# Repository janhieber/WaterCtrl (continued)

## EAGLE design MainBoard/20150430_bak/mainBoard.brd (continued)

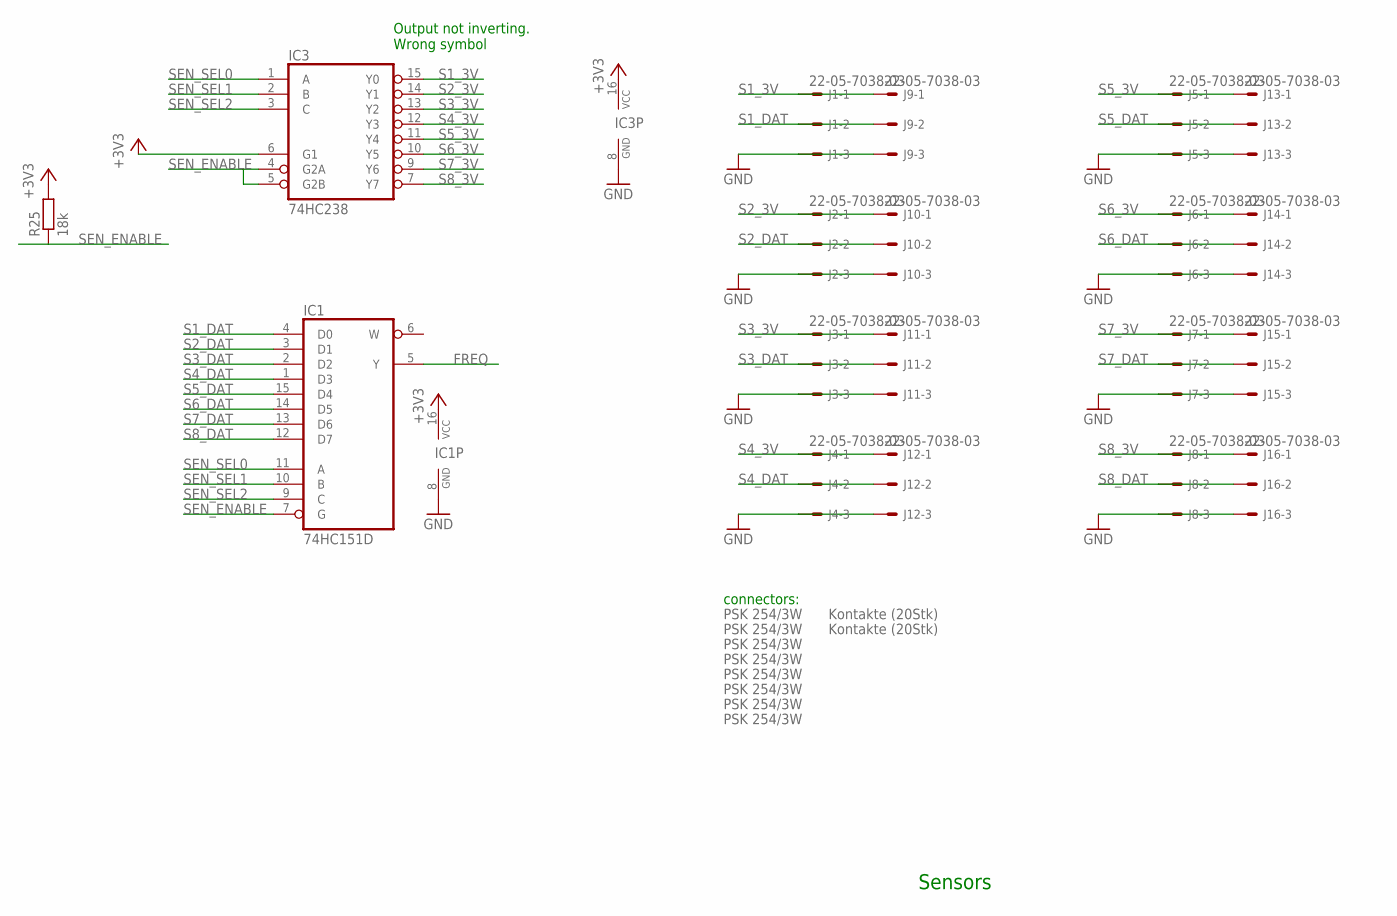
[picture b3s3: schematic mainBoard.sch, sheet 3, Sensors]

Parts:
IC1: 74HC151D; SO16
IC3: 74HC238; SO16
J1, J2, J3, J4, J5, J6, J7, J8, J9, J10, J11, J12, J13, J14, J15, J16: 22-05-7038-03; 7395-03
R25: 18k; R0805
U$3, U$4, U$5, U$6, U$7, U$8, U$9, U$10: PSK 254/3W; DUMMY_BOM
U$18, U$19: Kontakte (20Stk); DUMMY_BOM

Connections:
+3V3: IC1.16 (VCC), IC3.6 (G1), IC3.16 (VCC), R25.2; also elsewhere on the board
FREQ: IC1.5 (Y); also elsewhere on the board
GND: IC1.8 (GND), IC3.8 (GND), J1.3, J2.3, J3.3, J4.3, J5.3, J6.3, J7.3, J8.3, J9.3, J10.3, J11.3, J12.3, J13.3, J14.3, J15.3, J16.3; also elsewhere on the board
S1_3V: IC3.15 (Y0), J1.1, J9.1
S1_DAT: IC1.4 (D0), J1.2, J9.2
S2_3V: IC3.14 (Y1), J2.1, J10.1
S2_DAT: IC1.3 (D1), J2.2, J10.2
S3_3V: IC3.13 (Y2), J3.1, J11.1
S3_DAT: IC1.2 (D2), J3.2, J11.2
S4_3V: IC3.12 (Y3), J4.1, J12.1
S4_DAT: IC1.1 (D3), J4.2, J12.2
S5_3V: IC3.11 (Y4), J5.1, J13.1
S5_DAT: IC1.15 (D4), J5.2, J13.2
S6_3V: IC3.10 (Y5), J6.1, J14.1
S6_DAT: IC1.14 (D5), J6.2, J14.2
S7_3V: IC3.9 (Y6), J7.1, J15.1
S7_DAT: IC1.13 (D6), J7.2, J15.2
S8_3V: IC3.7 (Y7), J8.1, J16.1
S8_DAT: IC1.12 (D7), J8.2, J16.2
SEN_ENABLE: IC1.7 (G), IC3.4 (G2A), IC3.5 (G2B), R25.1; also elsewhere on the board
SEN_SEL0: IC1.11 (A), IC3.1 (A); also elsewhere on the board
SEN_SEL1: IC1.10 (B), IC3.2 (B); also elsewhere on the board
SEN_SEL2: IC1.9 (C), IC3.3 (C); also elsewhere on the board

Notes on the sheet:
Output not inverting. Wrong symbol
connectors:
Sensors

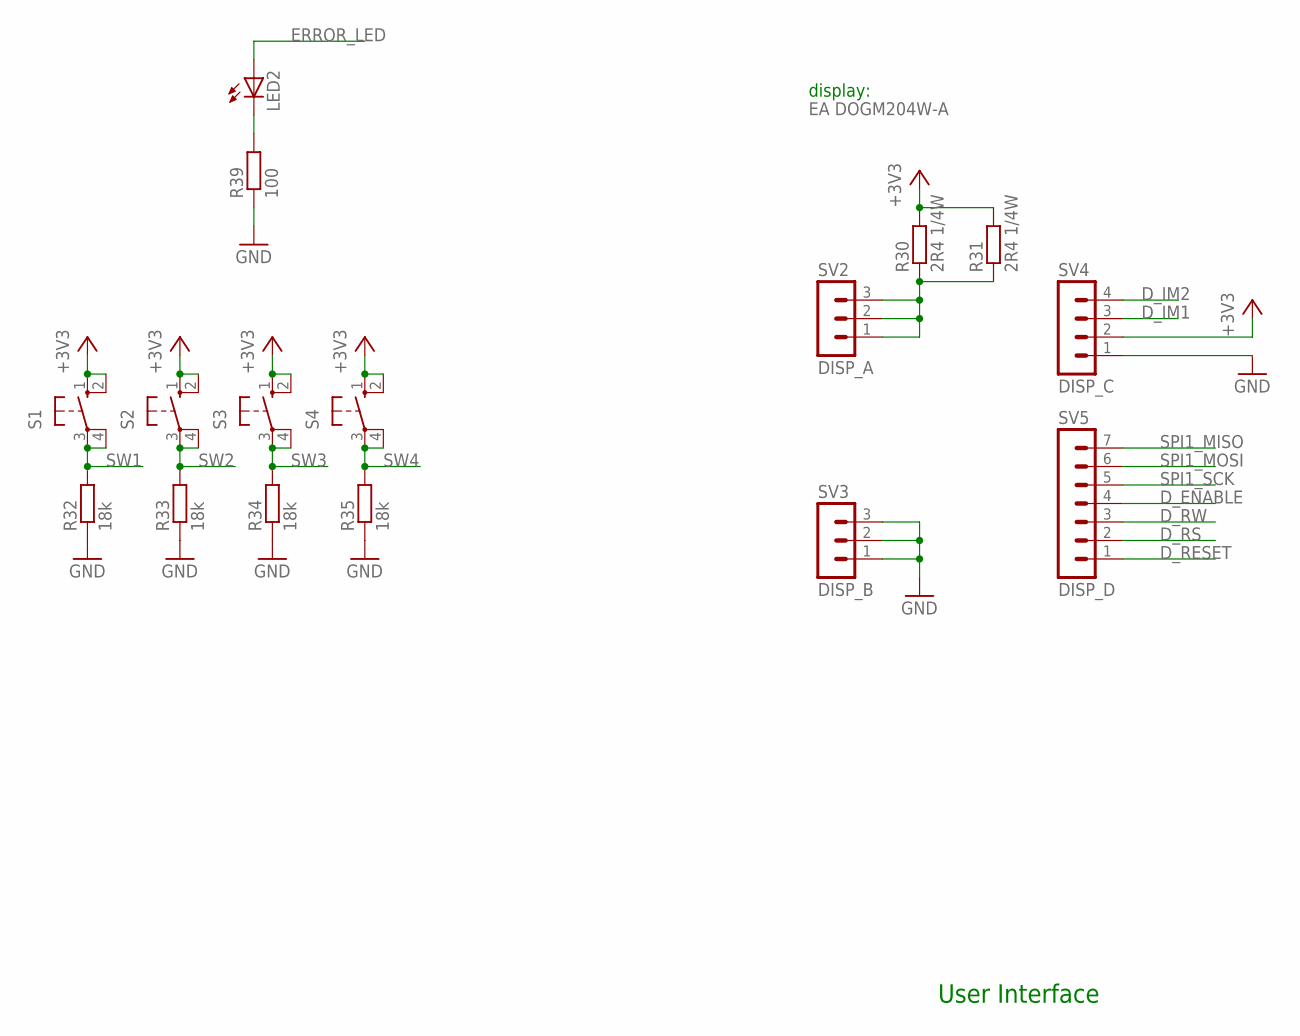
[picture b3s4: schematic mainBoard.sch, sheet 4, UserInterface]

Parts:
LED2: LED3MM
R30, R31: 2R4 1/4W; R1206
R32, R33, R34, R35: 18k; R0805
R39: 100; R0805
S1, S2, S3, S4: 10-XX; B3F-10XX
SV2: DISP_A; MA03-1
SV3: DISP_B; MA03-1
SV4: DISP_C; MA04-1
SV5: DISP_D; MA07-1
U$11: EA DOGM204W-A; DUMMY_BOM

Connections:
+3V3: R30.2, R31.2, S1.1 (S), S1.2 (S1), S2.1 (S), S2.2 (S1), S3.1 (S), S3.2 (S1), S4.1 (S), S4.2 (S1), SV4.2; also elsewhere on the board
D_ENABLE: SV5.4; also elsewhere on the board
D_IM1: SV4.3; also elsewhere on the board
D_IM2: SV4.4; also elsewhere on the board
D_RESET: SV5.1; also elsewhere on the board
D_RS: SV5.2; also elsewhere on the board
D_RW: SV5.3; also elsewhere on the board
ERROR_LED: LED2.A; also elsewhere on the board
GND: R32.1, R33.1, R34.1, R35.1, R39.1, SV3.1, SV3.2, SV3.3, SV4.1; also elsewhere on the board
unnamed: R30.1, R31.1, SV2.1, SV2.2, SV2.3
unnamed: LED2.K (C), R39.2
SPI1_MISO: SV5.7; also elsewhere on the board
SPI1_MOSI: SV5.6; also elsewhere on the board
SPI1_SCK: SV5.5; also elsewhere on the board
SW1: R32.2, S1.3, S1.4 (P1)
SW2: R33.2, S2.3, S2.4 (P1)
SW3: R34.2, S3.3, S3.4 (P1)
SW4: R35.2, S4.3, S4.4 (P1)

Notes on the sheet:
User Interface
display:

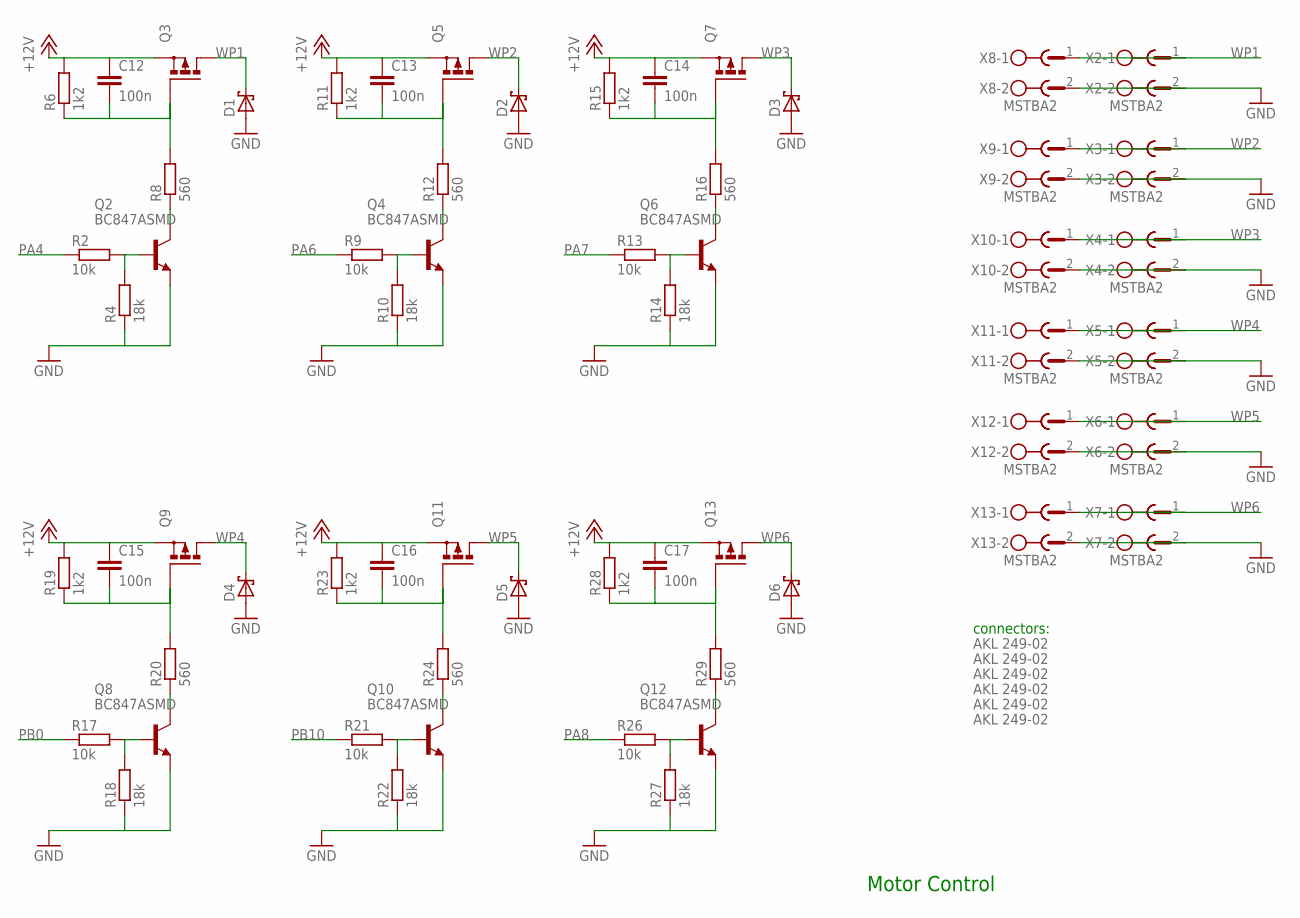
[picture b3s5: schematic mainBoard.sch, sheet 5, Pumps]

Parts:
C12, C13, C14, C15, C16, C17: 100n; C0805
D1, D2, D3, D4, D5, D6: SCHOTTKY-DIODESMC; SMC
Q2, Q4, Q6, Q8, Q10, Q12: BC847ASMD; SOT23
Q3, Q5, Q7, Q9, Q11, Q13: P-MOSFET-SO8; SO-08
R2, R9, R13, R17, R21, R26: 10k; R0805
R4, R10, R14, R18, R22, R27: 18k; R0805
R6, R11, R15, R19, R23, R28: 1k2; R0805
R8, R12, R16, R20, R24, R29: 560; R0805
U$12, U$13, U$14, U$15, U$16, U$17: AKL 249-02; DUMMY_BOM
X2, X3, X4, X5, X6, X7, X8, X9, X10, X11, X12, X13: MSTBA2

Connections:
+12V: C12.1, C13.1, C14.1, C15.1, C16.1, C17.1, Q3.1 (S), Q3.2 (S), Q3.3 (S), Q5.1 (S), Q5.2 (S), Q5.3 (S), Q7.1 (S), Q7.2 (S), Q7.3 (S), Q9.1 (S), Q9.2 (S), Q9.3 (S), Q11.1 (S), Q11.2 (S), Q11.3 (S), Q13.1 (S), Q13.2 (S), Q13.3 (S), R6.2, R11.2, R15.2, R19.2, R23.2, R28.2; also elsewhere on the board
GND: D1.A, D2.A, D3.A, D4.A, D5.A, D6.A, Q2.2 (E), Q4.2 (E), Q6.2 (E), Q8.2 (E), Q10.2 (E), Q12.2 (E), R4.1, R10.1, R14.1, R18.1, R22.1, R27.1, X2.2, X3.2, X4.2, X5.2, X6.2, X7.2, X8.2, X9.2, X10.2, X11.2, X12.2, X13.2; also elsewhere on the board
unnamed: C13.2, Q5.4 (G), R11.1, R12.2
unnamed: C12.2, Q3.4 (G), R6.1, R8.2
unnamed: Q2.3 (C), R8.1
unnamed: Q2.1 (B), R2.2, R4.2
unnamed: Q4.3 (C), R12.1
unnamed: Q4.1 (B), R9.2, R10.2
unnamed: C14.2, Q7.4 (G), R15.1, R16.2
unnamed: Q6.3 (C), R16.1
unnamed: Q6.1 (B), R13.2, R14.2
unnamed: C15.2, Q9.4 (G), R19.1, R20.2
unnamed: Q8.3 (C), R20.1
unnamed: Q8.1 (B), R17.2, R18.2
unnamed: C16.2, Q11.4 (G), R23.1, R24.2
unnamed: Q10.3 (C), R24.1
unnamed: Q10.1 (B), R21.2, R22.2
unnamed: C17.2, Q13.4 (G), R28.1, R29.2
unnamed: Q12.3 (C), R29.1
unnamed: Q12.1 (B), R26.2, R27.2
PA4: R2.1; also elsewhere on the board
PA6: R9.1; also elsewhere on the board
PA7: R13.1; also elsewhere on the board
PA8: R26.1; also elsewhere on the board
PB0: R17.1; also elsewhere on the board
PB10: R21.1; also elsewhere on the board
WP1: D1.C, Q3.5 (D), Q3.6 (D), Q3.7 (D), Q3.8 (D), X2.1, X8.1
WP2: D2.C, Q5.5 (D), Q5.6 (D), Q5.7 (D), Q5.8 (D), X3.1, X9.1
WP3: D3.C, Q7.5 (D), Q7.6 (D), Q7.7 (D), Q7.8 (D), X4.1, X10.1
WP4: D4.C, Q9.5 (D), Q9.6 (D), Q9.7 (D), Q9.8 (D), X5.1, X11.1
WP5: D5.C, Q11.5 (D), Q11.6 (D), Q11.7 (D), Q11.8 (D), X6.1, X12.1
WP6: D6.C, Q13.5 (D), Q13.6 (D), Q13.7 (D), Q13.8 (D), X7.1, X13.1

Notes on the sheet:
Motor Control
connectors:

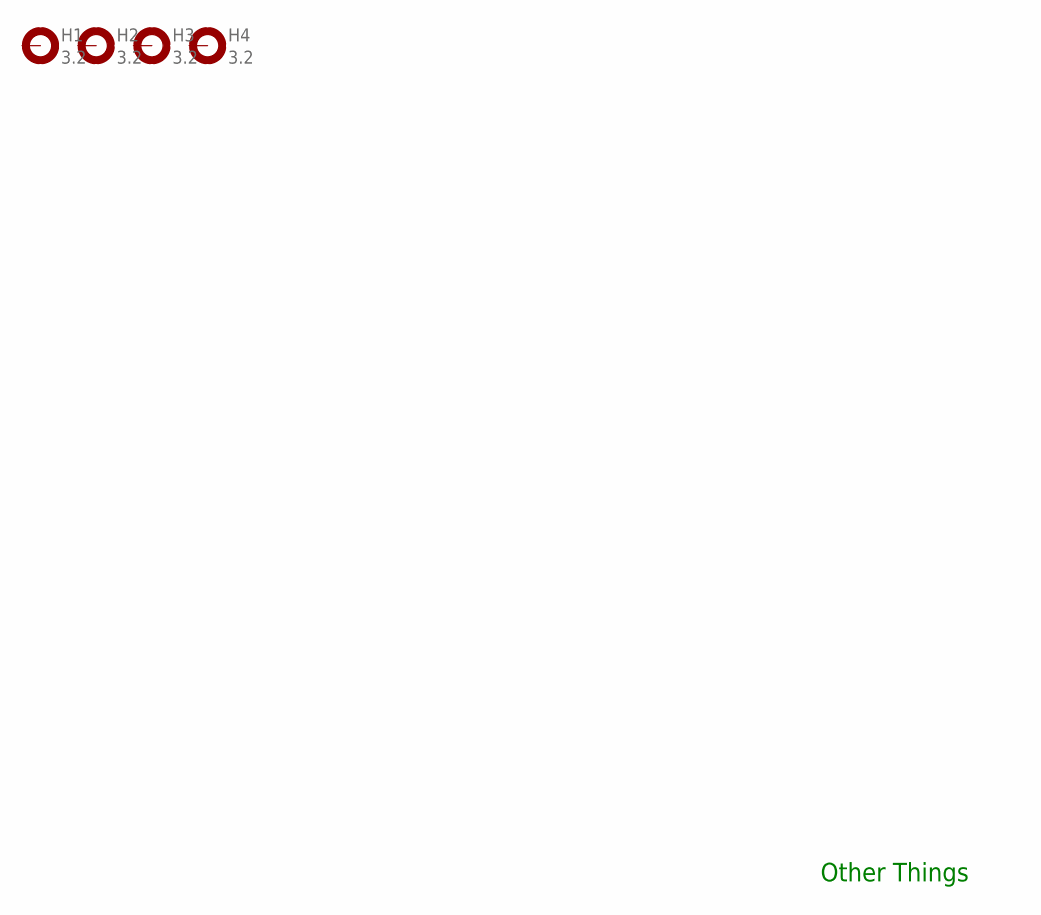
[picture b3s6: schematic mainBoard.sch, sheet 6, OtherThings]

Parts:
H1, H2, H3, H4: 3.2; 3,2-PAD

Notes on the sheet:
Other Things

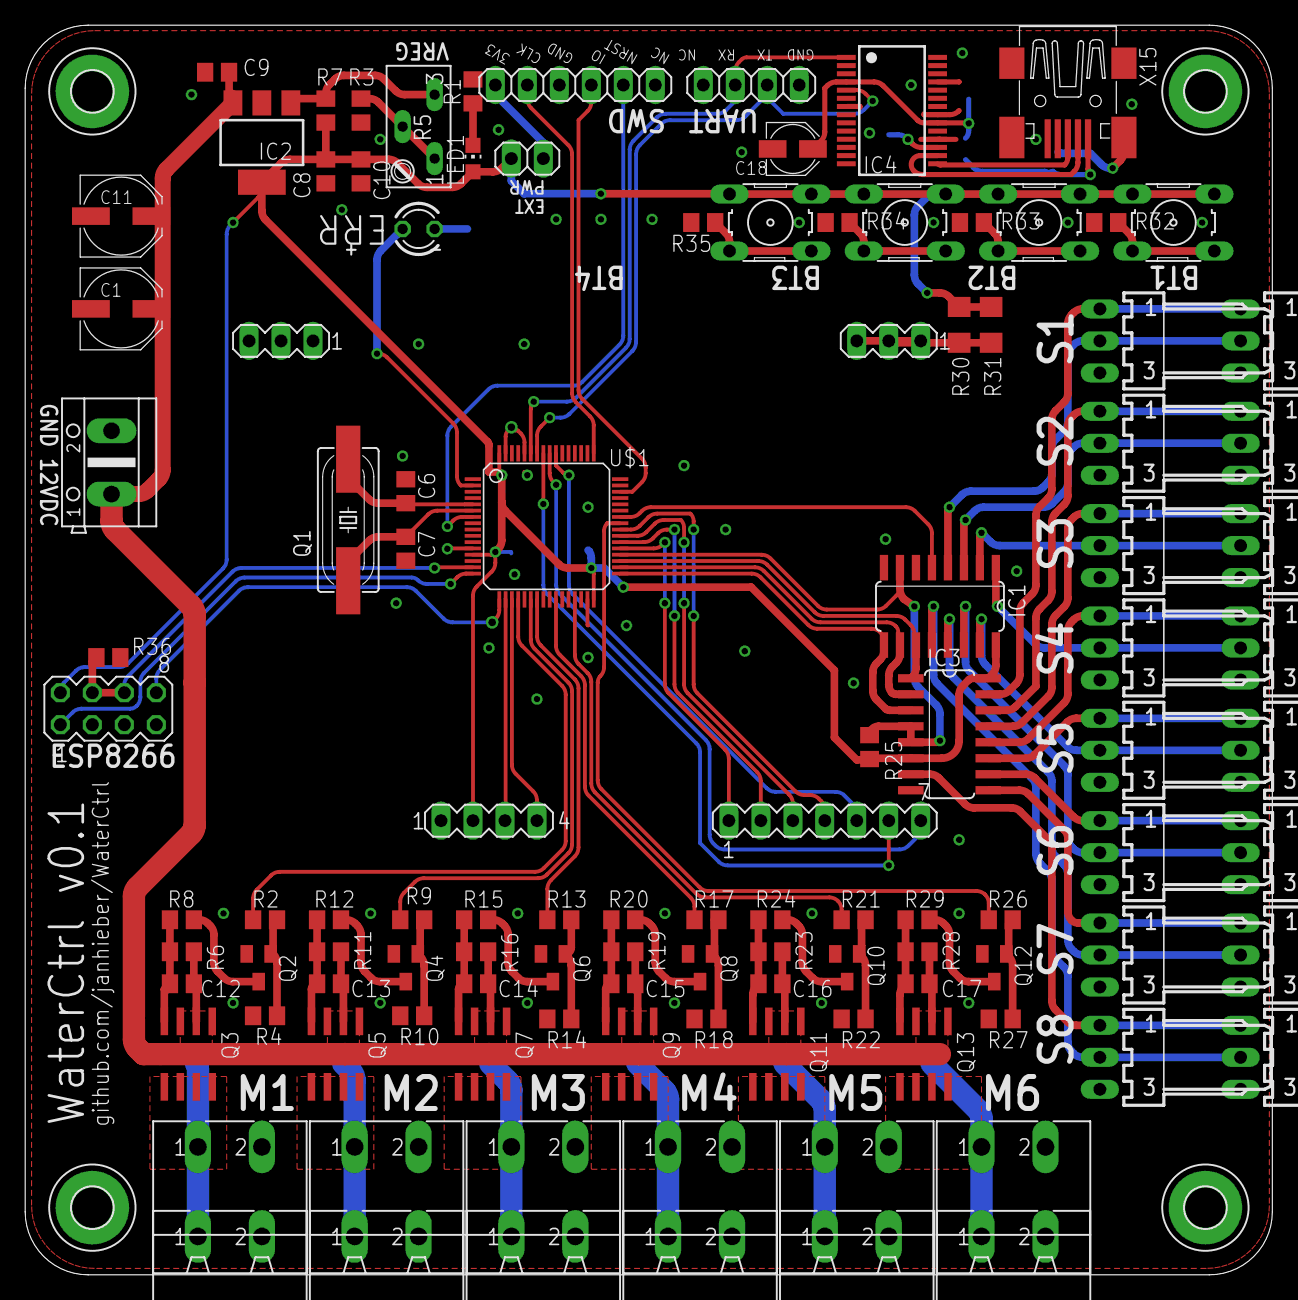
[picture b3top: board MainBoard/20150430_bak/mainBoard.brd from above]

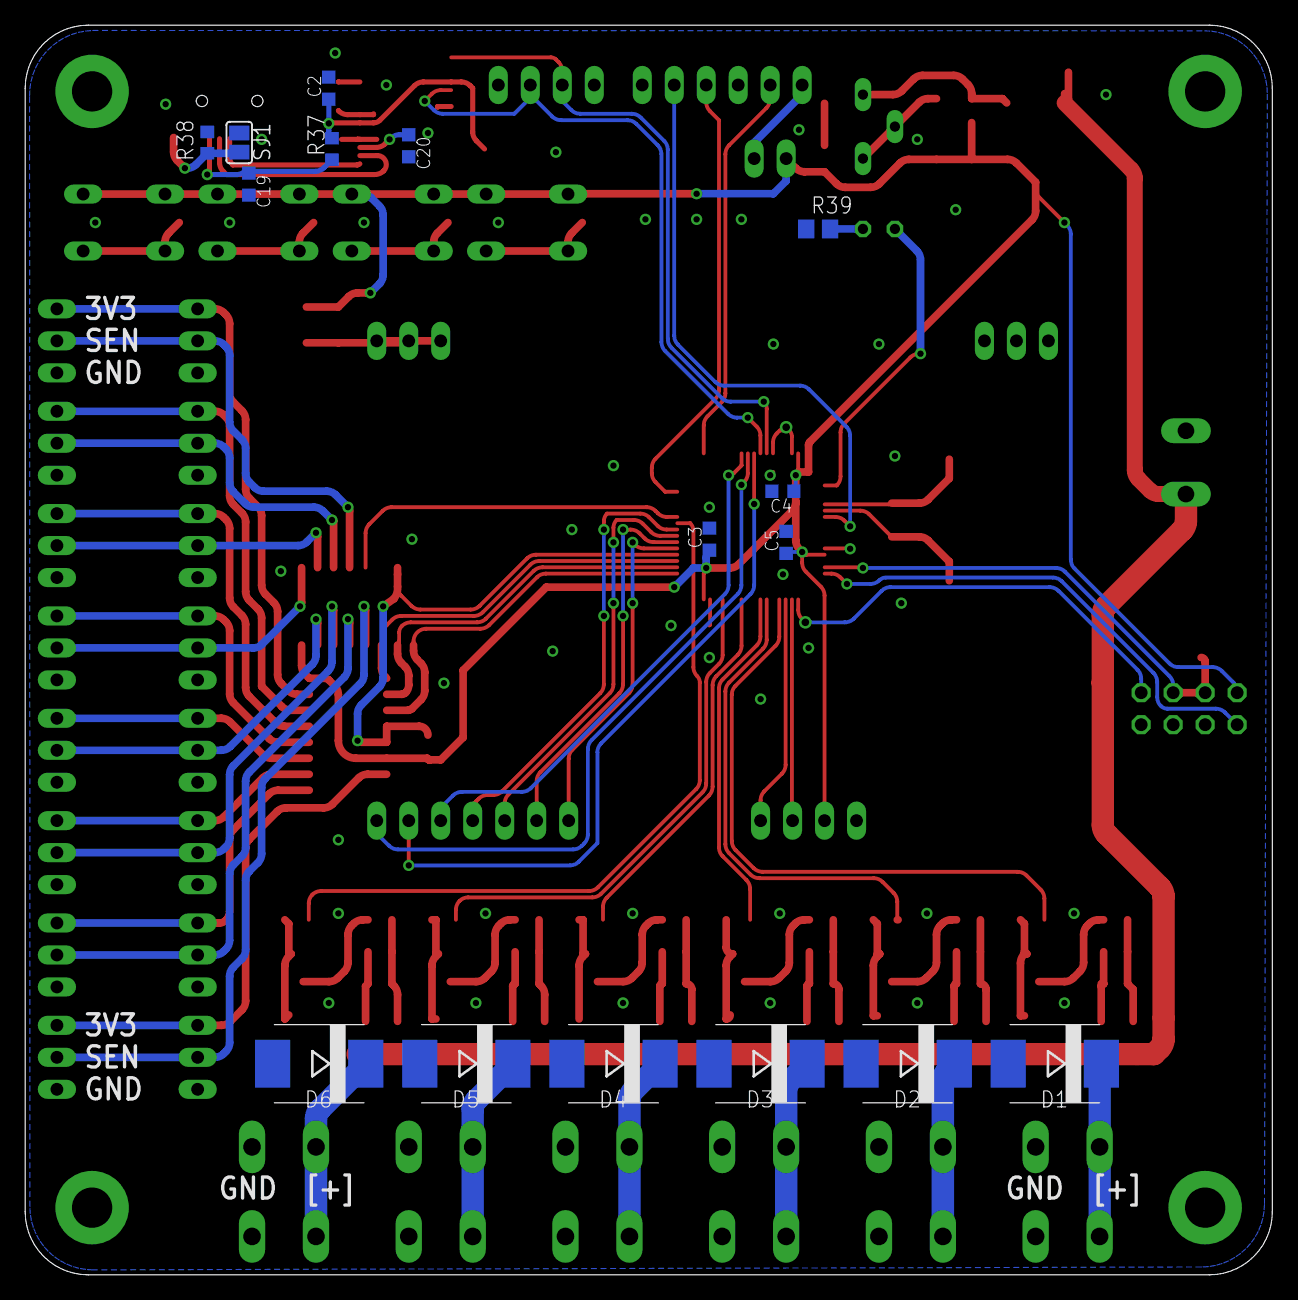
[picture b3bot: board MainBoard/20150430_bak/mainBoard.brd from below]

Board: 2 copper layers, 99.0 x 99.2 mm, 149 parts (16 on the bottom side), 90 nets.

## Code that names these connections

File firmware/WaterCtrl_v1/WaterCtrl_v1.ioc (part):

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Mcu.Name=STM32F103C(8-B)Tx
Mcu.Package=LQFP48
Mcu.UserName=STM32F103C8Tx
PA0-WKUP.GPIOParameters=GPIO_Speed,GPIO_Label,GPIO_ModeDefaultOutputPP
PA0-WKUP.GPIO_Label=PWM_A2
PA0-WKUP.GPIO_ModeDefaultOutputPP=GPIO_MODE_OUTPUT_PP
PA0-WKUP.GPIO_Speed=GPIO_SPEED_FREQ_LOW
PA0-WKUP.Signal=GPIO_Output
PA1.GPIOParameters=GPIO_ModeDefaultPP,GPIO_Speed,GPIO_Label
PA1.GPIO_Label=PWM
PA1.GPIO_ModeDefaultPP=GPIO_MODE_AF_PP
PA1.GPIO_Speed=GPIO_SPEED_FREQ_LOW
PA1.Signal=S_TIM2_CH2
PA10.Mode=Asynchronous
PA10.Signal=USART1_RX
PA13.Mode=Serial_Wire
PA13.Signal=SYS_JTMS-SWDIO
PA14.Mode=Serial_Wire
PA14.Signal=SYS_JTCK-SWCLK
PA2.GPIOParameters=GPIO_Label
PA2.GPIO_Label=ANALOG
PA2.Signal=ADCx_IN2
PA3.GPIOParameters=GPIO_PuPd,GPIO_Label
PA3.GPIO_Label=DHT22
PA3.GPIO_PuPd=GPIO_PULLUP
PA3.Signal=S_TIM2_CH4
PA5.Mode=Full_Duplex_Slave
PA5.Signal=SPI1_SCK
PA6.Mode=Full_Duplex_Slave
PA6.Signal=SPI1_MISO
PA7.Mode=Full_Duplex_Slave
PA7.Signal=SPI1_MOSI
PA9.Mode=Asynchronous
PA9.Signal=USART1_TX
PB0.GPIOParameters=GPIO_PuPd,GPIO_Label,GPIO_Mode
PB0.GPIO_Label=FREQ
PB0.GPIO_Mode=GPIO_MODE_INPUT
PB0.GPIO_PuPd=GPIO_PULLUP
PB0.Signal=S_TIM3_CH3
PB1.GPIOParameters=GPIO_Speed,GPIO_Label,GPIO_ModeDefaultOutputPP
PB1.GPIO_Label=SEN_A0
PB1.GPIO_ModeDefaultOutputPP=GPIO_MODE_OUTPUT_PP
PB1.GPIO_Speed=GPIO_SPEED_FREQ_LOW
PB1.Signal=GPIO_Output
PB10.GPIOParameters=GPIO_Speed,GPIO_Label,GPIO_ModeDefaultOutputPP
PB10.GPIO_Label=SEN_A1
PB10.GPIO_ModeDefaultOutputPP=GPIO_MODE_OUTPUT_PP
PB10.GPIO_Speed=GPIO_SPEED_FREQ_LOW
PB10.Signal=GPIO_Output
PB11.GPIOParameters=GPIO_Speed,GPIO_Label,GPIO_ModeDefaultOutputPP
PB11.GPIO_Label=SEN_A2
PB11.GPIO_ModeDefaultOutputPP=GPIO_MODE_OUTPUT_PP
PB11.GPIO_Speed=GPIO_SPEED_FREQ_LOW
PB11.Signal=GPIO_Output
PB15.GPIOParameters=GPIO_Speed,GPIO_Label,GPIO_ModeDefaultOutputPP
PB15.GPIO_Label=SEN_ENABLE
PB15.GPIO_ModeDefaultOutputPP=GPIO_MODE_OUTPUT_PP
PB15.GPIO_Speed=GPIO_SPEED_FREQ_LOW
PB15.Signal=GPIO_Output
PB3.GPIOParameters=PinState,GPIO_Label
PB3.GPIO_Label=RELAIS_0
PB3.PinState=GPIO_PIN_SET
PB3.Signal=GPIO_Output
PB4.GPIOParameters=PinState,GPIO_Label
PB4.GPIO_Label=RELAIS_1
PB4.PinState=GPIO_PIN_SET
PB4.Signal=GPIO_Output
PB5.GPIOParameters=PinState,GPIO_Label
PB5.GPIO_Label=RELAIS_2
PB5.PinState=GPIO_PIN_SET
PB5.Signal=GPIO_Output
PB6.GPIOParameters=PinState,GPIO_Label
PB6.GPIO_Label=RELAIS_3
PB6.PinState=GPIO_PIN_SET
PB6.Signal=GPIO_Output
PB7.GPIOParameters=PinState,GPIO_Label
PB7.GPIO_Label=RELAIS_4
PB7.PinState=GPIO_PIN_SET
PB7.Signal=GPIO_Output
PB9.GPIOParameters=GPIO_Speed,GPIO_Label,GPIO_ModeDefaultOutputPP
PB9.GPIO_Label=LED_ERR
PB9.GPIO_ModeDefaultOutputPP=GPIO_MODE_OUTPUT_PP
PB9.GPIO_Speed=GPIO_SPEED_FREQ_LOW
PB9.Signal=GPIO_Output
PC13-TAMPER-RTC.GPIOParameters=GPIO_Speed,GPIO_Label,GPIO_ModeDefaultOutputPP
PC13-TAMPER-RTC.GPIO_Label=RPI_NRST
PC13-TAMPER-RTC.GPIO_ModeDefaultOutputPP=GPIO_MODE_OUTPUT_OD
PC13-TAMPER-RTC.GPIO_Speed=GPIO_SPEED_FREQ_LOW
PC13-TAMPER-RTC.Signal=GPIO_Output
PC14-OSC32_IN.GPIOParameters=GPIO_Speed,GPIO_Label,GPIO_ModeDefaultOutputPP
PC14-OSC32_IN.GPIO_Label=PWM_A0
PC14-OSC32_IN.GPIO_ModeDefaultOutputPP=GPIO_MODE_OUTPUT_PP
PC14-OSC32_IN.GPIO_Speed=GPIO_SPEED_FREQ_LOW
PC14-OSC32_IN.Signal=GPIO_Output
PC15-OSC32_OUT.GPIOParameters=GPIO_Speed,GPIO_Label,GPIO_ModeDefaultOutputPP
PC15-OSC32_OUT.GPIO_Label=PWM_A1
PC15-OSC32_OUT.GPIO_ModeDefaultOutputPP=GPIO_MODE_OUTPUT_PP
PC15-OSC32_OUT.GPIO_Speed=GPIO_SPEED_FREQ_LOW
PC15-OSC32_OUT.Signal=GPIO_Output
PD0-OSC_IN.Mode=HSE-External-Oscillator
PD0-OSC_IN.Signal=RCC_OSC_IN
PD1-OSC_OUT.Mode=HSE-External-Oscillator
PD1-OSC_OUT.Signal=RCC_OSC_OUT
RCC.SYSCLKFreq_VALUE=72000000
RCC.SYSCLKSource=RCC_SYSCLKSOURCE_PLLCLK
board=WaterCtrl_v1

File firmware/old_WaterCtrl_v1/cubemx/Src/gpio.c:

/**
  ******************************************************************************
  * File Name          : gpio.c
  * Description        : This file provides code for the configuration
  *                      of all used GPIO pins.
  ******************************************************************************
  *
  * COPYRIGHT(c) 2016 STMicroelectronics
  *
  * Redistribution and use in source and binary forms, with or without modification,
  * are permitted provided that the following conditions are met:
  *   1. Redistributions of source code must retain the above copyright notice,
  *      this list of conditions and the following disclaimer.
  *   2. Redistributions in binary form must reproduce the above copyright notice,
  *      this list of conditions and the following disclaimer in the documentation
  *      and/or other materials provided with the distribution.
  *   3. Neither the name of STMicroelectronics nor the names of its contributors
  *      may be used to endorse or promote products derived from this software
  *      without specific prior written permission.
  *
  * THIS SOFTWARE IS PROVIDED BY THE COPYRIGHT HOLDERS AND CONTRIBUTORS "AS IS"
  * AND ANY EXPRESS OR IMPLIED WARRANTIES, INCLUDING, BUT NOT LIMITED TO, THE
  * IMPLIED WARRANTIES OF MERCHANTABILITY AND FITNESS FOR A PARTICULAR PURPOSE ARE
  * DISCLAIMED. IN NO EVENT SHALL THE COPYRIGHT HOLDER OR CONTRIBUTORS BE LIABLE
  * FOR ANY DIRECT, INDIRECT, INCIDENTAL, SPECIAL, EXEMPLARY, OR CONSEQUENTIAL
  * DAMAGES (INCLUDING, BUT NOT LIMITED TO, PROCUREMENT OF SUBSTITUTE GOODS OR
  * SERVICES; LOSS OF USE, DATA, OR PROFITS; OR BUSINESS INTERRUPTION) HOWEVER
  * CAUSED AND ON ANY THEORY OF LIABILITY, WHETHER IN CONTRACT, STRICT LIABILITY,
  * OR TORT (INCLUDING NEGLIGENCE OR OTHERWISE) ARISING IN ANY WAY OUT OF THE USE
  * OF THIS SOFTWARE, EVEN IF ADVISED OF THE POSSIBILITY OF SUCH DAMAGE.
  *
  ******************************************************************************
  */

/* Includes ------------------------------------------------------------------*/
#include "gpio.h"
/* USER CODE BEGIN 0 */

/* USER CODE END 0 */

/*----------------------------------------------------------------------------*/
/* Configure GPIO                                                             */
/*----------------------------------------------------------------------------*/
/* USER CODE BEGIN 1 */

/* USER CODE END 1 */

/** Configure pins as 
        * Analog 
        * Input 
        * Output
        * EVENT_OUT
        * EXTI
        * Free pins are configured automatically as Analog (this feature is enabled through 
        * the Code Generation settings)
*/
void MX_GPIO_Init(void)
{

  GPIO_InitTypeDef GPIO_InitStruct;

  /* GPIO Ports Clock Enable */
  __GPIOC_CLK_ENABLE();
  __GPIOD_CLK_ENABLE();
  __GPIOA_CLK_ENABLE();
  __GPIOB_CLK_ENABLE();

  /*Configure GPIO pin : PC13 */
  GPIO_InitStruct.Pin = GPIO_PIN_13;
  GPIO_InitStruct.Mode = GPIO_MODE_OUTPUT_OD;
  GPIO_InitStruct.Speed = GPIO_SPEED_LOW;
  HAL_GPIO_Init(GPIOC, &GPIO_InitStruct);

  /*Configure GPIO pins : PC14 PC15 */
  GPIO_InitStruct.Pin = GPIO_PIN_14|GPIO_PIN_15;
  GPIO_InitStruct.Mode = GPIO_MODE_OUTPUT_PP;
  GPIO_InitStruct.Speed = GPIO_SPEED_LOW;
  HAL_GPIO_Init(GPIOC, &GPIO_InitStruct);

  /*Configure GPIO pin : PA0 */
  GPIO_InitStruct.Pin = GPIO_PIN_0;
  GPIO_InitStruct.Mode = GPIO_MODE_OUTPUT_PP;
  GPIO_InitStruct.Speed = GPIO_SPEED_LOW;
  HAL_GPIO_Init(GPIOA, &GPIO_InitStruct);

  /*Configure GPIO pins : PA2 PA3 PA4 PA8 
                           PA11 PA12 PA15 */
  GPIO_InitStruct.Pin = GPIO_PIN_2|GPIO_PIN_3|GPIO_PIN_4|GPIO_PIN_8 
                          |GPIO_PIN_11|GPIO_PIN_12|GPIO_PIN_15;
  GPIO_InitStruct.Mode = GPIO_MODE_ANALOG;
  HAL_GPIO_Init(GPIOA, &GPIO_InitStruct);

  /*Configure GPIO pins : PB1 PB10 PB11 PB15 
                           PB9 */
  GPIO_InitStruct.Pin = GPIO_PIN_1|GPIO_PIN_10|GPIO_PIN_11|GPIO_PIN_15 
                          |GPIO_PIN_9;
  GPIO_InitStruct.Mode = GPIO_MODE_OUTPUT_PP;
  GPIO_InitStruct.Speed = GPIO_SPEED_LOW;
  HAL_GPIO_Init(GPIOB, &GPIO_InitStruct);

  /*Configure GPIO pins : PB2 PB12 PB13 PB14 
                           PB3 PB4 PB5 PB6 
                           PB7 PB8 */
  GPIO_InitStruct.Pin = GPIO_PIN_2|GPIO_PIN_12|GPIO_PIN_13|GPIO_PIN_14 
                          |GPIO_PIN_3|GPIO_PIN_4|GPIO_PIN_5|GPIO_PIN_6 
                          |GPIO_PIN_7|GPIO_PIN_8;
  GPIO_InitStruct.Mode = GPIO_MODE_ANALOG;
  HAL_GPIO_Init(GPIOB, &GPIO_InitStruct);

}

/* USER CODE BEGIN 2 */

/* USER CODE END 2 */

/**
  * @}
  */

/**
  * @}
  */

/************************ (C) COPYRIGHT STMicroelectronics *****END OF FILE****/

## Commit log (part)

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2015-03-30 add READMEs and a bit source
2015-03-30 fix READMEs
2015-03-30 some updates
2015-03-31 initial WebIf code. WARNING: not testet
2015-03-31 mainBoard updates
2015-03-31 some more main board updates
2015-03-31 update README file
2015-03-31 update gitignore
2015-03-31 mainBoard update
2015-03-31 parts and README update
2015-04-03 datamodel
    created enterprise architect data model
2015-04-03 data model
    refactoring
2015-04-05 mainboard updates...
2015-04-10 fw updates and docu
2015-04-10 doc updates
2015-04-11 data model
    added some attributes
    added documentation
    added png
2015-04-11 html
    dummy folder for html frontend
2015-04-12 moisture and main board updates
2015-04-13 mainboard silkscreen tuning
2015-04-14 MainBoard docu updates and prototype pics
2015-04-16 fix BOM generation; some board fixes
2015-04-17 Python REST API
    First version of the python REST API
2015-04-24 some initial firmware stuff
2015-04-27 Start of moisture measurement.
    Init capture compare input for PINA9. Add module api.
    Play with ignore files.
2015-04-28 Basic Frequency input proofed.
    Measure via interrupt one every 8t input event. Output in main loop.
    Untrack eclipse Debug folder and eclipse plugin settings.
2015-04-29 some documentation about design
2015-04-29 mainboard redesign ideas
2015-04-29 some docu stuff
2015-04-29 some thoughts about the future
2015-04-29 Initial AngularJS App
    AngularJS Frontend with Python REST Backend
2015-04-29 changed folder name
    changed folder name from HTTP_ROOT to Webserver
2015-04-29 changed folder name
2015-04-29 Frequency input
    Input from 30 kHz tp 800kHz working. Cyclic dump to printf.
2015-05-11 readme updates
2015-06-12 board STM32 update
2015-06-13 board updates, rpi and stm32
2015-06-13 generated FW
2015-06-13 board updates
2015-06-13 fw updates, generated code
2015-06-13 major readme updates
2015-06-13 docu updates
2015-06-13 fw project major changes for stm32cubemx
2015-06-14 cubemx proj update
2015-06-15 mainboard updates motor curcuit
2015-06-18 fw updates
2015-06-19 new image
2015-06-20 mainboard update + gerber export
2015-06-20 dirtypcbs order
2015-06-23 readme update
2015-06-24 board update
2015-06-26 continue readme file for raspberry pi
2015-06-26 added config attributes for the mysql database
2015-06-28 changed port for python web server
2015-06-28 some additional updates on the installation of the pi
2015-07-05 new PCBs!
2015-07-19 new base fw ready and working
2015-07-19 delete/ignore build folders
2015-07-19 update readme and fw
2015-07-20 UART printf and spi stuff
2015-07-22 Prepare multi sensor measurement.
2015-07-22 cubemx disable TIM4
2015-07-26 Removed hard coded paths from cproject file to fix build error on my dev host.
2015-07-26 Porting former code to new HAL structure. ISR not working yet. Callback not called, because interrupt not active.
2015-09-10 moved manual rpi linux setup
2015-09-20 New HAL generation to change the capture compare input filtering.
    To many inputs force to many interrupts and isr is never returned.
2015-10-08 some changes
2015-10-08 Closes #5 coded SPI
2015-10-08 migrate to new HAL lib
2015-10-08 add logging code files
2015-10-08 add header guards and file header comment
2015-10-08 chained queue for SPI queue, not tested yet
2015-10-08 OK, the chained lists may be too heavy, delete the whole stuff :/
2015-10-09 Create specification file
2015-10-10 start writing a scheduler. not finished yet
2015-10-15 convert from eclipse to coocox #1
2015-10-15 convert from eclipse to coocox #2
2015-10-15 convert from eclipse to coocox #3
2015-10-18 convert from eclipse to coocox FINISH :)
2015-10-19 some doxygen mods
2015-10-19 some code
2015-10-19 doxgen docu
2015-10-19 some fixes
2015-10-19 some SPI send recv stuff
2015-10-20 some QBS changes
2015-10-20 build and running. UART silent at moment. need investigation.
    Fix not running program by linking all object into one binary. No
    static library used any more.
2015-10-21 reenable moisture measurement. Delete not needed c-files via settings change in cubemx code generator.
    interrupts for TIM2&3 enabled and priorised between timer tick and spi interrupt.
2015-10-21 fix build.
2015-10-21 some QBS updates
2015-10-22 QBS changes
2015-10-22 fix warnings :)
2015-10-22 generate and test doxgen docs, call index.html
2015-10-22 fix doxygen comment stuff
2015-10-22 fix some bugs
2015-10-22 format files, clang-format Google style
2015-10-22 implement scheduling
2015-10-22 outsource scheduler and other stuff
2015-10-22 add independent watchdog, en/disable in mxconstants.h
2015-10-22 some codepath optimizations
2015-10-22 fix include
2015-10-22 forgot this in last commit :/
2015-10-22 added some usefull defines
2015-10-27 fix bug and add LogUart()
2015-10-27 some spi stuff
2015-10-27 create manual to setup QtCreator
2015-10-27 simplify build files
2015-10-27 random stuff ...
2015-10-27 RPI stuff
2015-10-30 SPI: some changes
2015-10-30 RPI: initial python daemon
2015-10-30 RPI: implement thread data exchange
2015-10-31 RPI: outsource some code, logger improvements
2015-10-31 RPI: some updates
2015-10-31 add config file ad database connection
2015-10-31 RPI minor changes
2015-11-02 start sensor multiplex. Still missing isr.
2015-11-04 put init code in extra files
2015-11-04 regen cubemx proj
2015-11-04 Start motor control
2015-11-04 add webinterface start script.
2015-11-04 image docu
2015-11-04 play with prescalars.
2015-11-04 script: preserve network links
2015-11-06 final timer setup.
2015-11-10 rewrite Log() function to printf arg style
2015-11-10 SPI ringbuffer changes
2015-11-10 SPI ringbuffer send working
2015-11-10 change to new log function
2015-11-10 RPI: MessageBroker working
2015-11-19 regen doxygen docu
2015-11-19 reformat code
2015-11-19 SPI: receive data
2015-11-19 RPI: send SPi data
2015-12-22 some docu
2015-12-22 board pic update
2015-12-22 moisture board small fixes
2016-01-11 update manual setup
2016-01-11 change CREATE TABLE SQL for PostgreSQL
2016-01-11 Regenerate with proper TIM3 and TIM2 settings.
2016-01-14 PWM sweep running. Fine tuned moisture sensor.
2016-01-14 PWM ramping.
2016-02-03 update specs
2016-02-15 move motors isr file in correct place. Correct max pulse width for ramp function.
2016-02-15 Broker for SPI message to moisture and motor done. Test to be done.
2016-02-21 ramps flank time implemented.
2016-02-22 Bugfixing ramp timing
2016-04-28 change db connection from mysql to postgresql
2016-05-07 extend gitignore for ignoring jetbrains project files and pyc files
2016-05-07 introduce sensor motor connection. sensors can have mutliple motors.
2016-05-07 remove sensor relationship with plants
2016-05-09 add logging entry in python script for a working script
2016-05-10 refactor stm32 system workbench readme for using local debugging
2016-05-10 fix IDE
2016-05-11 test send 0x12 via spi to stm32
2016-05-12 some minor changes in python watering script, same cycletime for both threads
2016-05-13 update spec
2016-05-13 FreeRTOS step 1
2016-05-13 FreeRTOS step 2
2016-05-13 FreeRTOS step 3. SPI thread does not work now. basics are working but unstable for now
2016-05-14 backup spi fix try
2016-05-14 Disable moisture and motor init. Try to ping pong SPI with rPi ends in endless loop
2016-05-14 add debugs into spi communication.
2016-05-14 spi ping working
2016-05-14 add 6 bytes constants to python script
2016-05-14 HardFault fixed in spi pool handling.
2016-05-15 prepare sensor and motor for new task concept
2016-05-15 moisture task working
2016-05-15 fine tune moisture
2016-05-15 fix sensor response and update spec
2016-05-16 add some postgresql doc
2016-05-16 refactor messagebroker spi logic
2016-05-16 fix hardfault in moisture request receive task
2016-05-16 Fix buffer overrun in spi
2016-05-16 Enable motor task
2016-05-16 add daemon start script
2016-05-16 Add dependencies to init script of waterctrl
2016-05-16 Add dependencies to init script webinterface
2016-05-16 Add daemon control service start to documentation
2016-05-17 add state machine diagram
2016-05-17 UML Usecases
2016-05-17 UML add components, broker and control states
2016-05-17 UML update broker
2016-05-23 add statemachine for watering logic
2016-06-03 add diagram for sensor values
2016-06-11 Increase stack and heap in linker file. Uncomment task creation.
    Build successfull, test outstanding.
2016-06-11 Set default task stack size to 64, like other tasks.
2016-06-11 Start dht22 implementation.
    Separate moisture from sensor. Add dht22 driver example from github and
    fix compile issues.
2016-06-11 Fit dht22 driver into operating system and current implementation rules.
    Change moisture measurement. Now the moisture task will not poll all
    sensore every second, it will measure one channel one second long. Get
    moisture function will block this seconds long. Moisture module must
    reconfigure the input pin, because its now share with dht22.
2016-06-12 Moisture measurement now on demand blocking.
2016-06-12 some further improvements to datamodel
2016-06-12 Daemon logging into temp folder
2016-06-12 Basic dht22 implementation done. New signaling to sensor needed. Communication with dht22 not working
2016-06-12 Fix system freeze with to many tasks
2016-06-13 Increase heap and shrink stack. Increase freertos head size.
2016-06-13 disable debug sensor reading
2016-06-14 fix error in watering inactive time
2016-06-15 Disable sensor when finished measurement.
    Play around with DHT22 pullup pin to test direct sensor signal line
    connected.
2016-06-15 Decrease sampling rate from 72MHz to 4MHz. Calc mean between current and last frequency value.
2016-06-17 add render sensor response diagram via chosen dates
2016-06-19 remove login module from ui
2016-06-19 Add Release build results
2016-12-28 Regenerate HAL with newest cubeMX (4.1.2) and firmware update.
    Release build running and measruing, motor control broken because interrupt is not handled.
    With new cubeMx/firmware mxconstants.h moved to main.h. ISR handling former worked after
    changing the generated source. this needs to be change by newer isr concept for all timers.
    DEBUG Build broken. STM32 in Timer isr loop when channel with real sensor connected gets
    triggered. SPI Broker escapes with full receive queue, looks like RTOS stopped working
    with heavy TIM3 ISR load.
2016-12-30 DHT22 working. Redefine timer clocks. Merge mxconstants into main.h.
2016-12-31 Refactoring for isr separation. Get motor output to work again.
2016-12-31 ADC input PA4 working. DFROBOT moisture sensor v1.0 ready.
    For testing, sensor 2 is hardcoded for ADC and sensor 1 is DHT22.
2017-01-01 implement 2. analog sensor type connected to FREQ input.
2017-01-01 Relais gpio configuration.
2017-01-01 Add relais request to spi broker.
2017-01-01 Add new relais module.
2017-01-06 Implement REST interface with flask and flask_restplus.
2017-01-11 Remove flask_restplus.
2017-01-25 Create ARCH Linux for ARM based rpi image.
    - shall install to get flask running with python3.
    - new REST service to control sensor types and relais.
2017-01-27 update docu after upload.
2017-01-31 Disable logfile, logging now via journalctl. Change to longer measurement cycle. Update requirements.
2017-01-31 Update database password. Implement clear and set via GET and DELETE.
2017-02-06 mplement response SPI to REST.
2017-02-11 REST: start and stop motor: STM: bugfixing, stop motor. Change analog sensor calaculation.
2017-02-12 Bugfixing.
2017-02-12 Changed stop motor implmenetation.
2017-02-12 Easy sensor value.
2017-02-12 Fix 2. analog channel input.
2017-02-12 Fix warnings.
2017-02-12 Implement GET sensor to read the sensors value. Implement PUT sensor type to change the sensors type.
2017-02-21 More Error Handling.
2017-02-21 Increase task stack size to fix debug build goes stack overflow.
2017-02-21 Fix sensor type.
2017-02-21 Fix sensor type change.
2017-02-21 Rebuild Release.
2017-03-01 swagger API documentation is back. flask_restplus needed from now on. Add relais table to database via pgadmin3 and update SQL model. Add data seed for new table.
2018-01-01 Update swagger for relais and motors.
2018-01-03 Implement Sensor WebService to seperate control daemon from spi.
